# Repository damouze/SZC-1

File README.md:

# The Stackable Z80 Computer

A layman's attempt at designing a modular, stackable Z80 computer.

## Disclaimer

Let me start by pointing out that I am not an electronic engineer. Everything I know
about electronics I learned from the internet and from two electronic design courses
during my university days, and nearly all of it is theoretical. I am really more of a
software person who decided at one point in his not-so-distant past that it might be
fun to start learning to design (digital) electronic circuits. 

That said, this is not my first KiCAD project. 

The designs in this repository are bound to have many, many flaws, and I would love to
hear about them from you. Just keep in mind that I do have a day job and that it takes
precedence if I do not respond to them within a day. As a person without an actual
background in electronic design I am sure I am making assumptions about components in
the design that are incorrect or otherwise potentially troublesome. 

Ok, enough ranting. Let's have a look at it.

## Physical description

In principle, the Stackable Z80 computer is more an idea than an actual design. As such
it is built around the following concepts:

- The board dimensions are 95.25mm x 95.25mm (3.75" x 3.75")
- There are four main connectors:
    - Expansion Connector A (2x20 pins, IDC)
	- Expansion Connector B (2x17 pins, IDC)
	- Expansion Connector C (2x4 pins, IDC)
	- Power Connector (2x10 pins, IDC)
- Each board can be stacked on top of another through the use of standoffs

Expansion Connector A is standardized; it contains most, if not all, of the relevant
Z80 signals, such as the address bus (A0-A15), the data bus (D0-D7), control signals
like /INT, /RESET, etc, and both a CPU_CLK and a BUS_CLK signal (they may differ, but
the former should then always be an integer multiple of the latter). All address, data
and control lines should have pull-ups or pull-downs on at least one board, so as to
prevent undesirable current from flowing between two devices asserting the bus at the
same time. They are also buffered. Pins 1 and 40 are connected to ground.

Expansion Connector B is partly standardized; the uneven numbered pins are used for 8
interrupt lines (/INT0-/INT7), as well as 8 more address lines (MA14-A21). Pins 1 and 
34 are connected to ground. The remaining pins, all even, are defined as USER0-USER15,
or in other words, user defined. 

Expansion Connector C contains the extra bus signals provided by the Z80 CPU board with
an extended bus (cpu_board_ext_bus+v2). It provides 5 new signals: /IOR, /IOW, /MEMR, /MEMW
and /INTA. These can be used to simplify the designs of future boards. In addition they
also provide the necessary signals for interfacing with an Intel 8259 Programmable
Interrupt Controller. 

The Power Connector is standardized around the 20-pins ATX power supply connector, and indeed
the Power Board does contain one, but power to the CPU board is provided through an IDC header.
The rationale behind this is that power to the CPU board is is delivered from the power supply 
through the power board, which has a front panel header and which in turn distributes power to
the CPU board through the aforementioned 2x10 pins IDC header.

Power delivery to all other boards is standardized around the old-fashioned floppy 
connector (TE_171826-4). Only +12V and +5V are available. +5VSB (standby power) and 3.3V
should be delivered separately, for instance from the power board.

## Minimal configuration (top to bottom)

- Serial I/O board
- ROM/RAM board
- The "even simpler Z80" board
- Power board V2

This will provide a basic Z80 system with serial I/O support. The serial I/O board should
be configured to use /INT as its interrupt line and use 0x80 as its I/O base address.

The system will have 32kB of ROM, as well as 96kB of RAM, able to be paged in or out of the
Z80 address space as needed in segments of 16kB. 

Expansion Bus B is not used in this configuration.

## A more advance configuration (top to bottom)

- Serial I/O board
- ROM/RAM board v2
- CPU board with expansion Connector C
- Power board V2

This will provide a slightly more advanced Z80 system with serial I/O support. The serial I/O
board should be configured to use /INT as its interrupt line and use 0x80 as its I/O
base address. The ROM/RAM board should be configured for Bank 0. 

This system will have 512kB of Flash ROM and 1536kB of SRAM. Segments 0-31 will be ROM, 
segments 32-127 will be RAM. Segments 128-255 will be available for add-on boards with
their own ROM or RAM or which use memory mapped I/O. 

## Repository layout
 
The repository is laid out as follows:

- boards/core contains the core boards
    - even_simpler_z80: the basic, bare bones Z80 board; just the CPU, some buffers/latches and a clock generator
	- power_board: the power delivery board
	- power_board_v2: and updated version of the power delivery board, with power-on circuitry onboard
	- rom_ram_board: a board that provides 32kB of ROM and 96kB of RAM, able to be paged in and out as needed
	- serial_io_board: a board that provides a RS232 interface for outside communication
- boards/extra contains some extra board designs
    - 8259_pic_board: 8259 Interrupt Controller Board for the SZC-1; requires Expansion Connector C
    - audio_board: SSG Audio Board for the SZC-1, providing SSG sound support
	- cpu_board_ext_bus_v2: new and improved CPU board providing Expansion Connector C and an on-board memory mapper
    - diag_board: a basic diagnostics board, providing a 2-digit 7-segment display accessible through I/O port 0xb8
	- ide_board: IDE Board for the SZC-1, inspired by the Beer IDE interface for the MSX
	- mmu_board: a preliminary design for a Z80 MMU built around a ATF1502/1504 CPLD (*work in progress*)
	- rom_ram_board_2MB: a board that provides 512kB of flash ROM and 1536kB of RAM, able to be paged in and out as needed
	- rom_ram_board_128kB_v2: another board that provides 32kB of EEPROM and 96kB of RAM; requires Expansion Connector C
	- rom_ram_board_v2: another board that provides 512kB of flash ROM and 1536kB of RAM; requires Expansion Connector C
	- simple_z80: the original Z80 board, CPU, buffers/latches and a LS74xx based IM2 interrupt controller
- boards/msx_compat contains boards to provide MSX compatibility (*work in progress*)
    - msx_rom_board: a board that houses to 32kB EEPROM sockets for MSX compatible ROMs (requires the ppi_slot_select_expanded board)
    - msx_rom_ram_board: a board with 512kB flash ROM and 1MB SRAM (requires the ppi_slot_select_expanded board)
	- ppi_slot_select: a board that provides MSX compatible slot select registers as well as 16 GPIO pins
	- ppi_slot_select_expanded: as ppi_slot_select, but also contains an expanded slot select register
- digital contains experiments made in Digital to work out some concepts
- doc: contains documentation and other reference material
- ibom: interactive BOMs for the boards
- pics: 
    - renderings: contains 3D renderings of most of the boards
	- photos: contains photos of PCBs and assembled boards
- verilog: contains verilog output from Digital for the experiments in the *digital* folder.

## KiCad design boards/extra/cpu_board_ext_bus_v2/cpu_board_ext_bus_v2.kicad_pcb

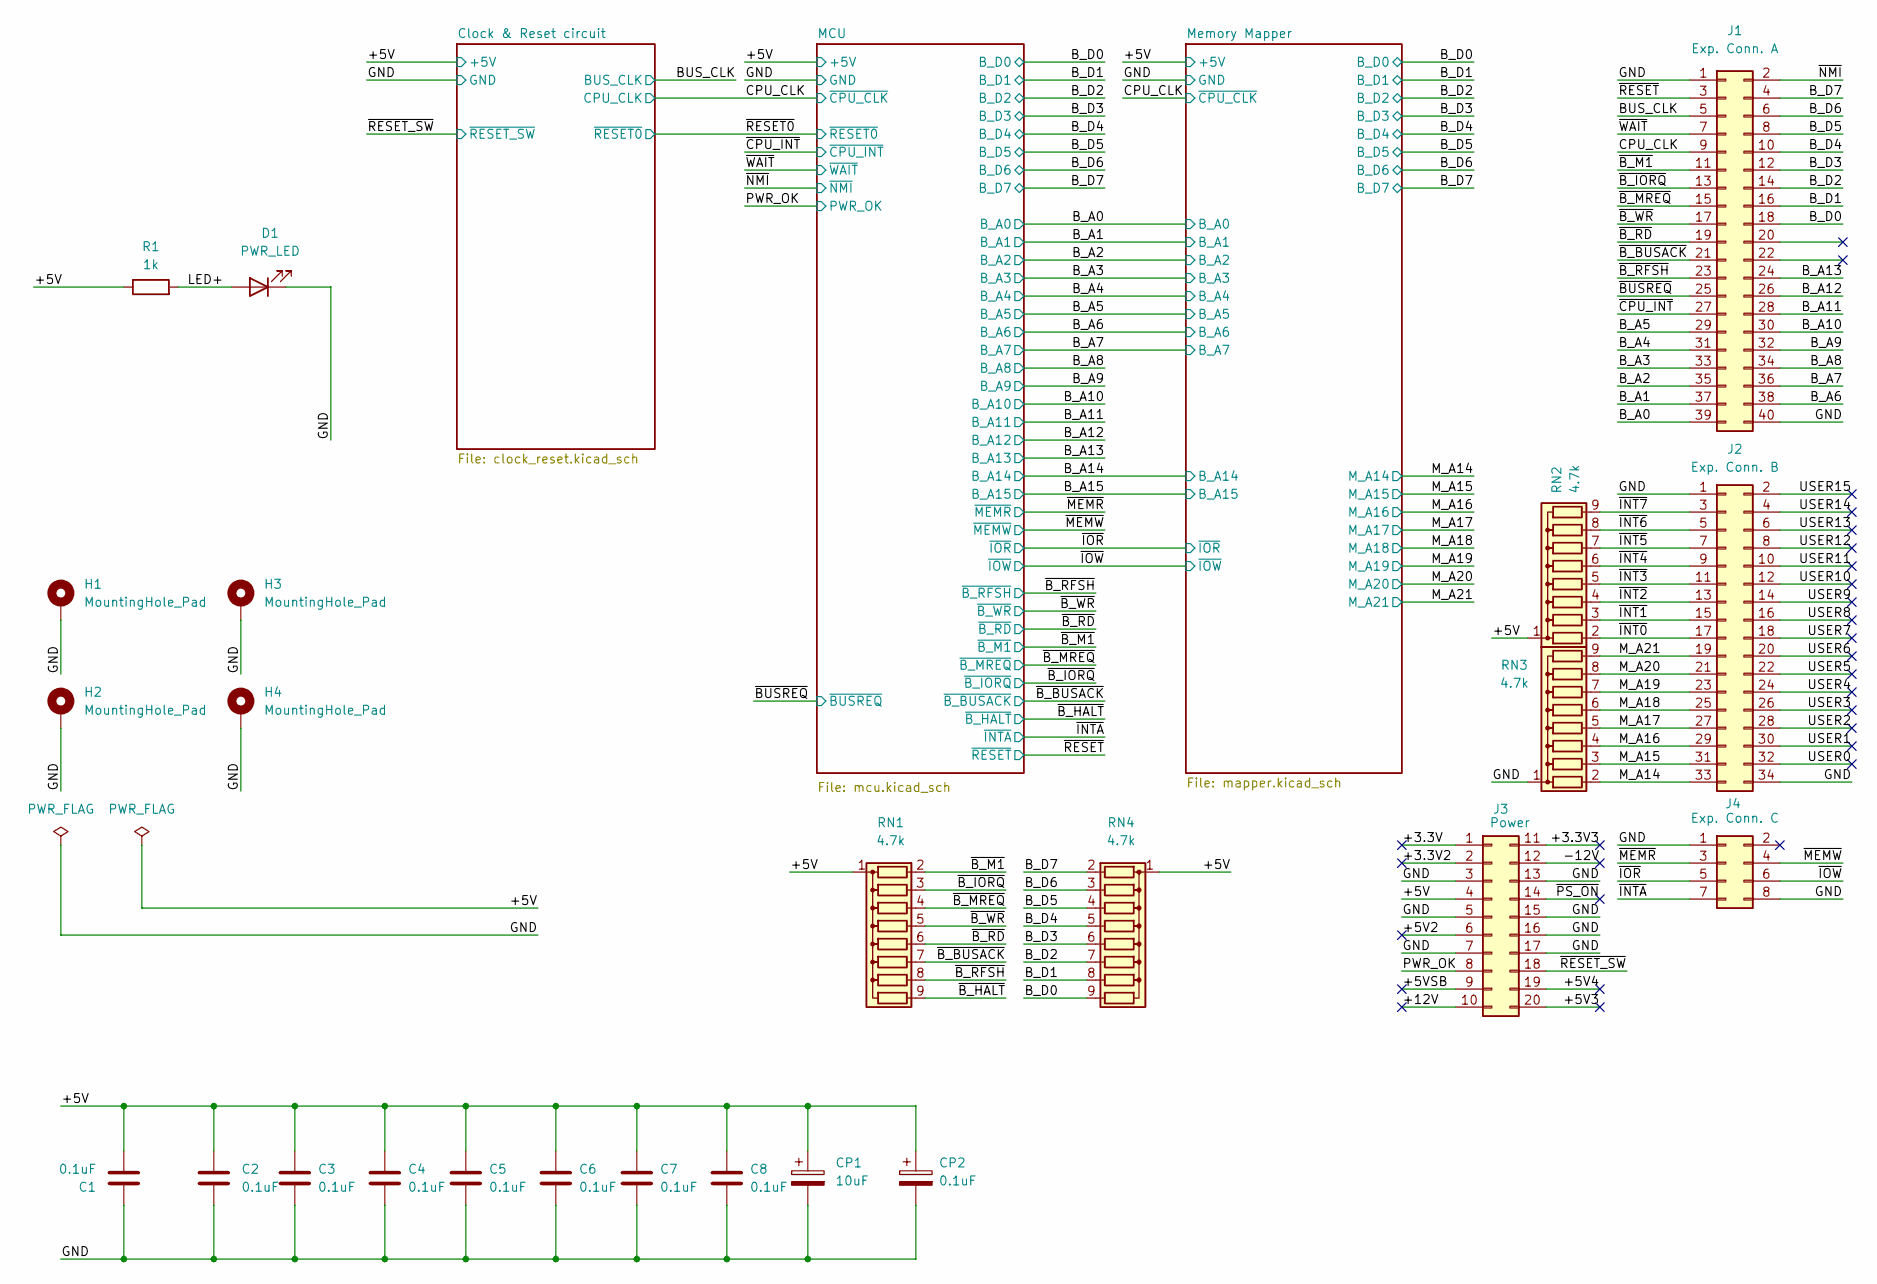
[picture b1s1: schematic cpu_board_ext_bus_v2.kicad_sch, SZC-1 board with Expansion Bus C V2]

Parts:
C1, C2, C3, C4, C5, C6, C7, C8: 0.1uF; C_Disc_D5.0mm_W2.5mm_P2.50mm; MPN FG28X7R1H104KNT06
CP1: 10uF; CP_Radial_D5.0mm_P2.50mm; MPN ECA1HM100I
CP2: 0.1uF; CP_Radial_D5.0mm_P2.50mm; MPN KS104M050C07RR0VH2FP0
D1: PWR_LED; LED_D3.0mm; MPN HLMP-1700
H1, H2, H3, H4: MountingHole_Pad; MountingHole_3.2mm_M3_ISO7380_Pad
J1: Exp. Conn. A; IDC-Header_2x20_P2.54mm_Horizontal; MPN X9555WR-2x20-6TV01
J2: Exp. Conn. B; IDC-Header_2x17_P2.54mm_Horizontal; MPN X9555WR-2x17-6TV01
J3: Power; IDC-Header_2x10_P2.54mm_Horizontal; MPN X9555WR-2x10-6TV01
J4: Exp. Conn. C; IDC-Header_2x04_P2.54mm_Horizontal; MPN 75867-132LF
R1: 1k; R_Axial_DIN0204_L3.6mm_D1.6mm_P7.62mm_Horizontal; MPN MBA02040C1001FC100
RN1, RN2, RN3, RN4: 4.7k; R_Array_SIP9; MPN A09-472JP

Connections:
/+3.3V: J3.1
/+3.3V2: J3.2
/+3.3V3: J3.11
/+5V: C1.1, C2.1, C3.1, C4.1, C5.1, C6.1, C7.1, C8.1, CP1.1, CP2.1, J3.4, R1.1, RN1.1 (common), RN2.1 (common), RN4.1 (common); also elsewhere on the board
/+5V2: J3.6
/+5V3: J3.20
/+5V4: J3.19
/+5VSB: J3.9
/+12V: J3.10
/-12V: J3.12
/BUS_CLK: J1.5; also elsewhere on the board
/B_A0: J1.39; also elsewhere on the board
/B_A1: J1.37; also elsewhere on the board
/B_A2: J1.35; also elsewhere on the board
/B_A3: J1.33; also elsewhere on the board
/B_A4: J1.31; also elsewhere on the board
/B_A5: J1.29; also elsewhere on the board
/B_A6: J1.38; also elsewhere on the board
/B_A7: J1.36; also elsewhere on the board
/B_A8: J1.34; also elsewhere on the board
/B_A9: J1.32; also elsewhere on the board
/B_A10: J1.30; also elsewhere on the board
/B_A11: J1.28; also elsewhere on the board
/B_A12: J1.26; also elsewhere on the board
/B_A13: J1.24; also elsewhere on the board
/B_D0: J1.18, RN4.9 (R8); also elsewhere on the board
/B_D1: J1.16, RN4.8 (R7); also elsewhere on the board
/B_D2: J1.14, RN4.7 (R6); also elsewhere on the board
/B_D3: J1.12, RN4.6 (R5); also elsewhere on the board
/B_D4: J1.10, RN4.5 (R4); also elsewhere on the board
/B_D5: J1.8, RN4.4 (R3); also elsewhere on the board
/B_D6: J1.6, RN4.3 (R2); also elsewhere on the board
/B_D7: J1.4, RN4.2 (R1); also elsewhere on the board
/CPU_CLK: J1.9; also elsewhere on the board
/GND: C1.2, C2.2, C3.2, C4.2, C5.2, C6.2, C7.2, C8.2, CP1.2, CP2.2, D1.1 (K), H1.1, H2.1, H3.1, H4.1, J1.1, J1.40, J2.1, J2.34, J3.3, J3.5, J3.7, J3.13, J3.15, J3.16, J3.17, J4.1, J4.8, RN3.1 (common); also elsewhere on the board
/LED+: D1.2 (A), R1.2
/M_A14: J2.33, RN3.2 (R1); also elsewhere on the board
/M_A15: J2.31, RN3.3 (R2); also elsewhere on the board
/M_A16: J2.29, RN3.4 (R3); also elsewhere on the board
/M_A17: J2.27, RN3.5 (R4); also elsewhere on the board
/M_A18: J2.25, RN3.6 (R5); also elsewhere on the board
/M_A19: J2.23, RN3.7 (R6); also elsewhere on the board
/M_A20: J2.21, RN3.8 (R7); also elsewhere on the board
/M_A21: J2.19, RN3.9 (R8); also elsewhere on the board
/PWR_OK: J3.8; also elsewhere on the board
/USER0: J2.32
/USER1: J2.30
/USER2: J2.28
/USER3: J2.26
/USER4: J2.24
/USER5: J2.22
/USER6: J2.20
/USER7: J2.18
/USER8: J2.16
/USER9: J2.14
/USER10: J2.12
/USER11: J2.10
/USER12: J2.8
/USER13: J2.6
/USER14: J2.4
/USER15: J2.2
/~BUSREQ: J1.25; also elsewhere on the board
/~B_BUSACK: J1.21, RN1.7 (R6); also elsewhere on the board
/~B_HALT: RN1.9 (R8); also elsewhere on the board
/~B_IORQ: J1.13, RN1.3 (R2); also elsewhere on the board
/~B_M1: J1.11, RN1.2 (R1); also elsewhere on the board
/~B_MREQ: J1.15, RN1.4 (R3); also elsewhere on the board
/~B_RD: J1.19, RN1.6 (R5); also elsewhere on the board
/~B_RFSH: J1.23, RN1.8 (R7); also elsewhere on the board
/~B_WR: J1.17, RN1.5 (R4); also elsewhere on the board
/~CPU_INT: J1.27; also elsewhere on the board
/~INT0: J2.17, RN2.2 (R1)
/~INT1: J2.15, RN2.3 (R2)
/~INT2: J2.13, RN2.4 (R3)
/~INT3: J2.11, RN2.5 (R4)
/~INT4: J2.9, RN2.6 (R5)
/~INT5: J2.7, RN2.7 (R6)
/~INT6: J2.5, RN2.8 (R7)
/~INT7: J2.3, RN2.9 (R8)
/~INTA: J4.7; also elsewhere on the board
/~IOR: J4.5; also elsewhere on the board
/~IOW: J4.6; also elsewhere on the board
/~MEMR: J4.3; also elsewhere on the board
/~MEMW: J4.4; also elsewhere on the board
/~NMI: J1.2; also elsewhere on the board
/~PS_ON: J3.14
/~RESET_SW: J3.18; also elsewhere on the board
/~RESET: J1.3; also elsewhere on the board
/~WAIT: J1.7; also elsewhere on the board

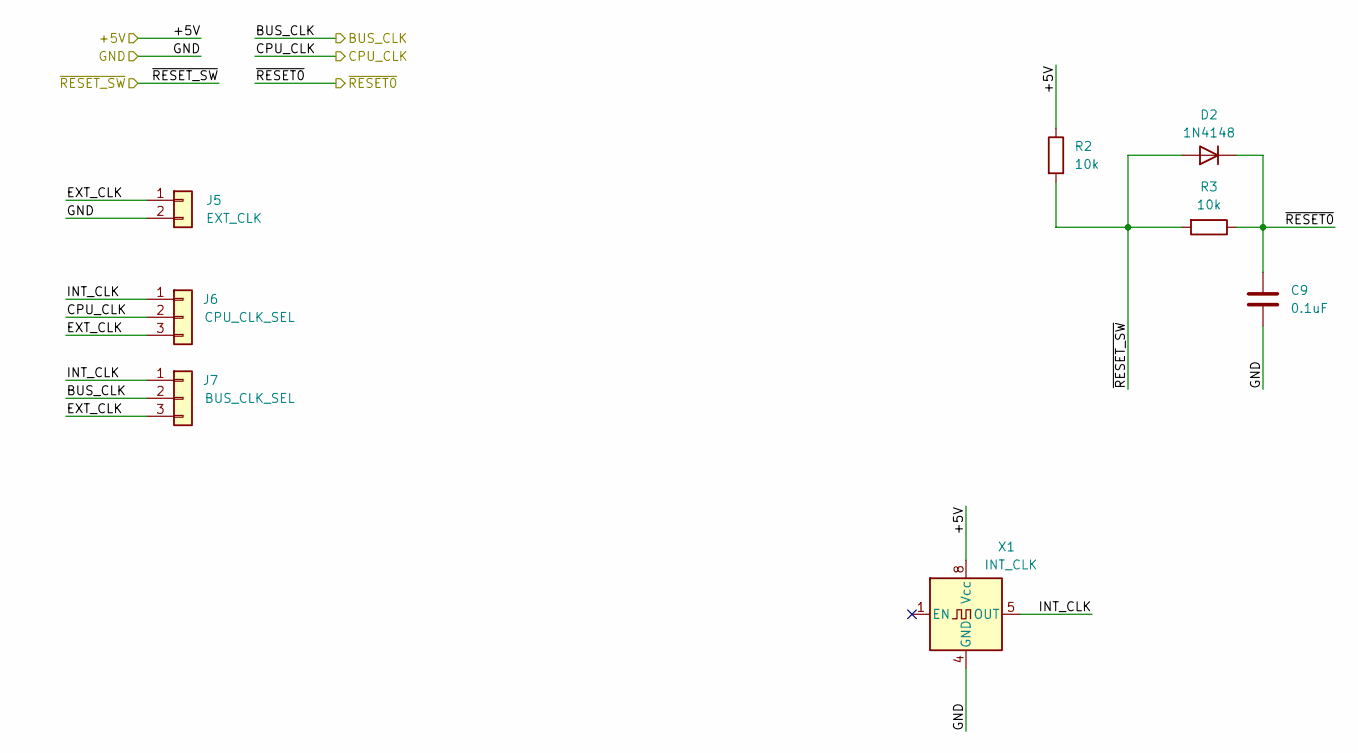
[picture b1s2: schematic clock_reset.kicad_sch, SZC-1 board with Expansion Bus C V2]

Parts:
C9: 0.1uF; C_Disc_D5.0mm_W2.5mm_P2.50mm; MPN FG28X7R1H104KNT06
D2: 1N4148; D_DO-35_SOD27_P7.62mm_Horizontal; MPN 1N4148TA
J5: EXT_CLK; PinHeader_1x02_P2.54mm_Horizontal; MPN PZ254R-11-02P
J6: CPU_CLK_SEL; PinHeader_1x03_P2.54mm_Horizontal; MPN PZ254R-11-03P
J7: BUS_CLK_SEL; PinHeader_1x03_P2.54mm_Horizontal; MPN PZ254R-11-03P
R2, R3: 10k; R_Axial_DIN0204_L3.6mm_D1.6mm_P7.62mm_Horizontal; MPN MBA02040C1002FRP00
X1: INT_CLK; Oscillator_DIP-8; MPN 1-2199298-2

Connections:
/+5V: R2.1, X1.8 (Vcc); also elsewhere on the board
/BUS_CLK: J7.2; also elsewhere on the board
/CPU_CLK: J6.2; also elsewhere on the board
/Clock & Reset circuit/EXT_CLK: J5.1, J6.3, J7.3
/Clock & Reset circuit/INT_CLK: J6.1, J7.1, X1.5 (OUT)
/GND: C9.2, J5.2, X1.4 (GND); also elsewhere on the board
/~RESET0: C9.1, D2.1 (K), R3.1; also elsewhere on the board
/~RESET_SW: D2.2 (A), R2.2, R3.2; also elsewhere on the board

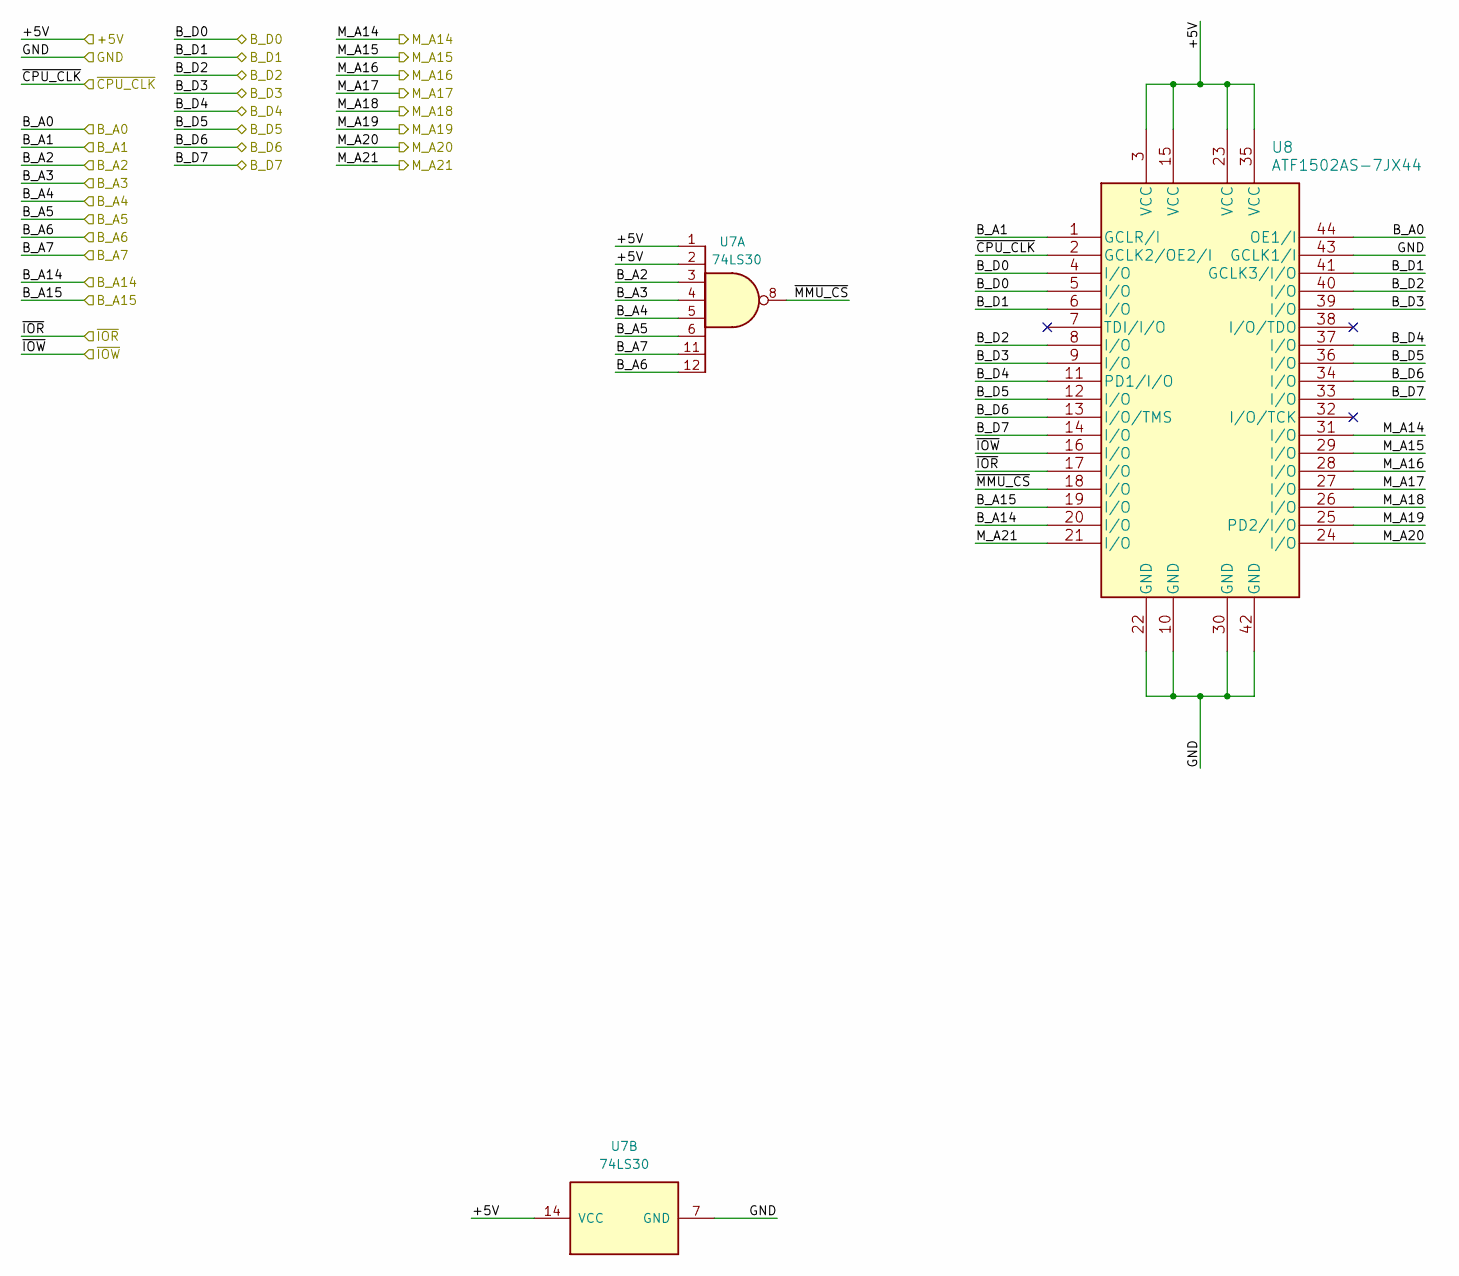
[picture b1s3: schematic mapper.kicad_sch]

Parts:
U7: 74LS30; DIP-14_W7.62mm_Socket; MPN 1-2199298-3
U8: ATF1502AS-7JX44; PLCC-44_THT-Socket; MPN DS1032-44SDKT1A

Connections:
/+5V: U7.1, U7.2, U7.14 (VCC), U8.3 (VCC), U8.15 (VCC), U8.23 (VCC), U8.35 (VCC); also elsewhere on the board
/B_A0: U8.44 (OE1/I); also elsewhere on the board
/B_A1: U8.1 (GCLR/I); also elsewhere on the board
/B_A2: U7.3; also elsewhere on the board
/B_A3: U7.4; also elsewhere on the board
/B_A4: U7.5; also elsewhere on the board
/B_A5: U7.6; also elsewhere on the board
/B_A6: U7.12; also elsewhere on the board
/B_A7: U7.11; also elsewhere on the board
/B_A14: U8.20 (I/O); also elsewhere on the board
/B_A15: U8.19 (I/O); also elsewhere on the board
/B_D0: U8.4 (I/O), U8.5 (I/O); also elsewhere on the board
/B_D1: U8.6 (I/O), U8.41 (GCLK3/I/O); also elsewhere on the board
/B_D2: U8.8 (I/O), U8.40 (I/O); also elsewhere on the board
/B_D3: U8.9 (I/O), U8.39 (I/O); also elsewhere on the board
/B_D4: U8.11 (PD1/I/O), U8.37 (I/O); also elsewhere on the board
/B_D5: U8.12 (I/O), U8.36 (I/O); also elsewhere on the board
/B_D6: U8.13 (I/O/TMS), U8.34 (I/O); also elsewhere on the board
/B_D7: U8.14 (I/O), U8.33 (I/O); also elsewhere on the board
/CPU_CLK: U8.2 (GCLK2/OE2/I); also elsewhere on the board
/GND: U7.7 (GND), U8.10 (GND), U8.22 (GND), U8.30 (GND), U8.42 (GND), U8.43 (GCLK1/I); also elsewhere on the board
/M_A14: U8.31 (I/O); also elsewhere on the board
/M_A15: U8.29 (I/O); also elsewhere on the board
/M_A16: U8.28 (I/O); also elsewhere on the board
/M_A17: U8.27 (I/O); also elsewhere on the board
/M_A18: U8.26 (I/O); also elsewhere on the board
/M_A19: U8.25 (PD2/I/O); also elsewhere on the board
/M_A20: U8.24 (I/O); also elsewhere on the board
/M_A21: U8.21 (I/O); also elsewhere on the board
/Memory Mapper/~MMU_CS: U7.8, U8.18 (I/O)
/~IOR: U8.17 (I/O); also elsewhere on the board
/~IOW: U8.16 (I/O); also elsewhere on the board

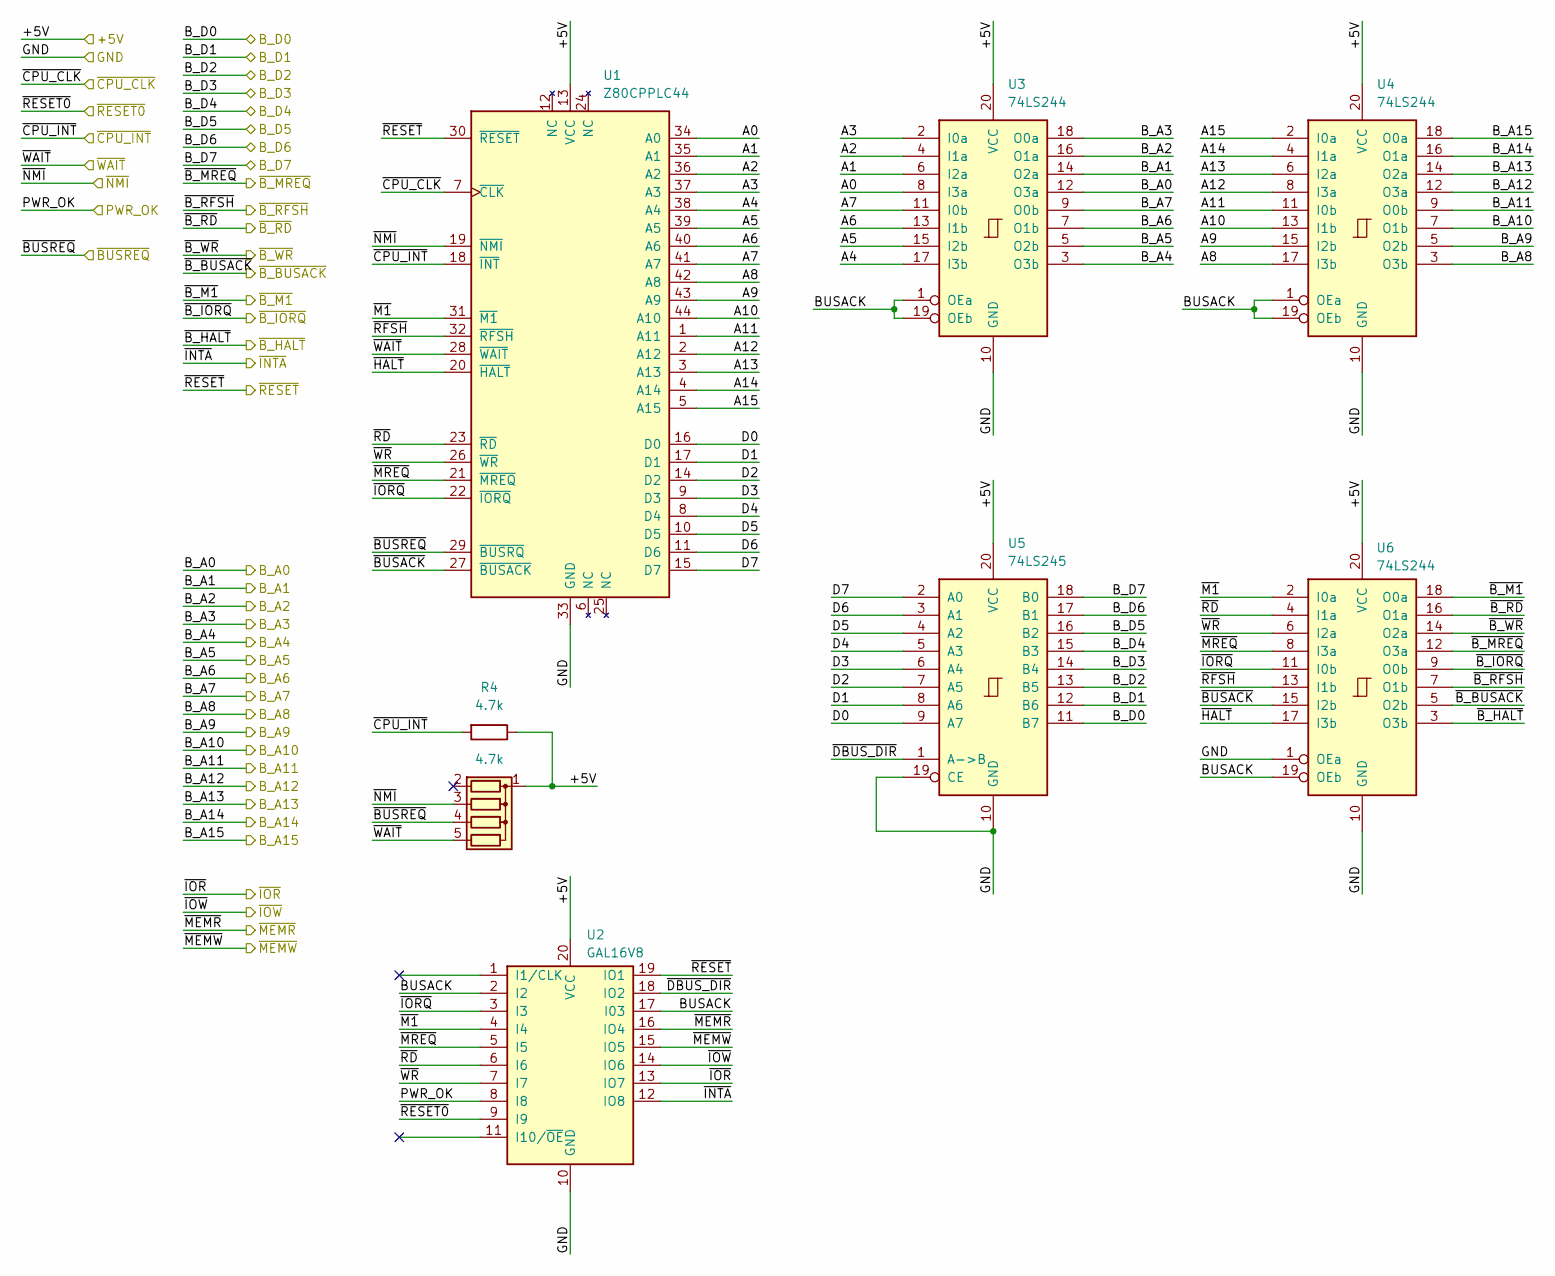
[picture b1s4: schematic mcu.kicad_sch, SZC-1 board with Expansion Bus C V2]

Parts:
R4: 4.7k; R_Axial_DIN0204_L3.6mm_D1.6mm_P7.62mm_Horizontal; MPN MF0207FTE52-4K7
RN5: 4.7k; R_Array_SIP5; MPN A05-472JP
U1: Z80CPPLC44; PLCC-44_THT-Socket; MPN DS1032-44SDKT1A
U2: GAL16V8; DIP-20_W7.62mm_Socket; MPN 1-2199298-6
U3, U4, U6: 74LS244; DIP-20_W7.62mm_Socket; MPN 1-2199298-6
U5: 74LS245; DIP-20_W7.62mm_Socket; MPN 1-2199298-6

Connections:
/+5V: R4.1, RN5.1 (common), U1.13 (VCC), U2.20 (VCC), U3.20 (VCC), U4.20 (VCC), U5.20 (VCC), U6.20 (VCC); also elsewhere on the board
/B_A0: U3.12 (O3a); also elsewhere on the board
/B_A1: U3.14 (O2a); also elsewhere on the board
/B_A2: U3.16 (O1a); also elsewhere on the board
/B_A3: U3.18 (O0a); also elsewhere on the board
/B_A4: U3.3 (O3b); also elsewhere on the board
/B_A5: U3.5 (O2b); also elsewhere on the board
/B_A6: U3.7 (O1b); also elsewhere on the board
/B_A7: U3.9 (O0b); also elsewhere on the board
/B_A8: U4.3 (O3b); also elsewhere on the board
/B_A9: U4.5 (O2b); also elsewhere on the board
/B_A10: U4.7 (O1b); also elsewhere on the board
/B_A11: U4.9 (O0b); also elsewhere on the board
/B_A12: U4.12 (O3a); also elsewhere on the board
/B_A13: U4.14 (O2a); also elsewhere on the board
/B_A14: U4.16 (O1a); also elsewhere on the board
/B_A15: U4.18 (O0a); also elsewhere on the board
/B_D0: U5.11 (B7); also elsewhere on the board
/B_D1: U5.12 (B6); also elsewhere on the board
/B_D2: U5.13 (B5); also elsewhere on the board
/B_D3: U5.14 (B4); also elsewhere on the board
/B_D4: U5.15 (B3); also elsewhere on the board
/B_D5: U5.16 (B2); also elsewhere on the board
/B_D6: U5.17 (B1); also elsewhere on the board
/B_D7: U5.18 (B0); also elsewhere on the board
/CPU_CLK: U1.7 (~CLK); also elsewhere on the board
/GND: U1.33 (GND), U2.10 (GND), U3.10 (GND), U4.10 (GND), U5.10 (GND), U5.19 (CE), U6.1 (OEa), U6.10 (GND); also elsewhere on the board
/MCU/A0: U1.34 (A0), U3.8 (I3a)
/MCU/A1: U1.35 (A1), U3.6 (I2a)
/MCU/A2: U1.36 (A2), U3.4 (I1a)
/MCU/A3: U1.37 (A3), U3.2 (I0a)
/MCU/A4: U1.38 (A4), U3.17 (I3b)
/MCU/A5: U1.39 (A5), U3.15 (I2b)
/MCU/A6: U1.40 (A6), U3.13 (I1b)
/MCU/A7: U1.41 (A7), U3.11 (I0b)
/MCU/A8: U1.42 (A8), U4.17 (I3b)
/MCU/A9: U1.43 (A9), U4.15 (I2b)
/MCU/A10: U1.44 (A10), U4.13 (I1b)
/MCU/A11: U1.1 (A11), U4.11 (I0b)
/MCU/A12: U1.2 (A12), U4.8 (I3a)
/MCU/A13: U1.3 (A13), U4.6 (I2a)
/MCU/A14: U1.4 (A14), U4.4 (I1a)
/MCU/A15: U1.5 (A15), U4.2 (I0a)
/MCU/BUSACK: U2.2 (I2), U2.17 (I03), U3.1 (OEa), U3.19 (OEb), U4.1 (OEa), U4.19 (OEb), U6.19 (OEb)
/MCU/D0: U1.16 (D0), U5.9 (A7)
/MCU/D1: U1.17 (D1), U5.8 (A6)
/MCU/D2: U1.14 (D2), U5.7 (A5)
/MCU/D3: U1.9 (D3), U5.6 (A4)
/MCU/D4: U1.8 (D4), U5.5 (A3)
/MCU/D5: U1.10 (D5), U5.4 (A2)
/MCU/D6: U1.11 (D6), U5.3 (A1)
/MCU/D7: U1.15 (D7), U5.2 (A0)
/MCU/~BUSACK: U1.27 (~BUSACK), U6.15 (I2b)
/MCU/~DBUS_DIR: U2.18 (IO2), U5.1 (A->B)
/MCU/~HALT: U1.20 (~HALT), U6.17 (I3b)
/MCU/~IORQ: U1.22 (~IORQ), U2.3 (I3), U6.11 (I0b)
/MCU/~M1: U1.31 (~M1), U2.4 (I4), U6.2 (I0a)
/MCU/~MREQ: U1.21 (~MREQ), U2.5 (I5), U6.8 (I3a)
/MCU/~RD: U1.23 (~RD), U2.6 (I6), U6.4 (I1a)
/MCU/~RFSH: U1.32 (~RFSH), U6.13 (I1b)
/MCU/~WR: U1.26 (~WR), U2.7 (I7), U6.6 (I2a)
/PWR_OK: U2.8 (I8); also elsewhere on the board
/~BUSREQ: RN5.4 (R3), U1.29 (~BUSRQ); also elsewhere on the board
/~B_BUSACK: U6.5 (O2b); also elsewhere on the board
/~B_HALT: U6.3 (O3b); also elsewhere on the board
/~B_IORQ: U6.9 (O0b); also elsewhere on the board
/~B_M1: U6.18 (O0a); also elsewhere on the board
/~B_MREQ: U6.12 (O3a); also elsewhere on the board
/~B_RD: U6.16 (O1a); also elsewhere on the board
/~B_RFSH: U6.7 (O1b); also elsewhere on the board
/~B_WR: U6.14 (O2a); also elsewhere on the board
/~CPU_INT: R4.2, U1.18 (~INT); also elsewhere on the board
/~INTA: U2.12 (IO8); also elsewhere on the board
/~IOR: U2.13 (IO7); also elsewhere on the board
/~IOW: U2.14 (IO6); also elsewhere on the board
/~MEMR: U2.16 (IO4); also elsewhere on the board
/~MEMW: U2.15 (IO5); also elsewhere on the board
/~NMI: RN5.3 (R2), U1.19 (~NMI); also elsewhere on the board
/~RESET0: U2.9 (I9); also elsewhere on the board
/~RESET: U1.30 (~RESET), U2.19 (IO1); also elsewhere on the board
/~WAIT: RN5.5 (R4), U1.28 (~WAIT); also elsewhere on the board

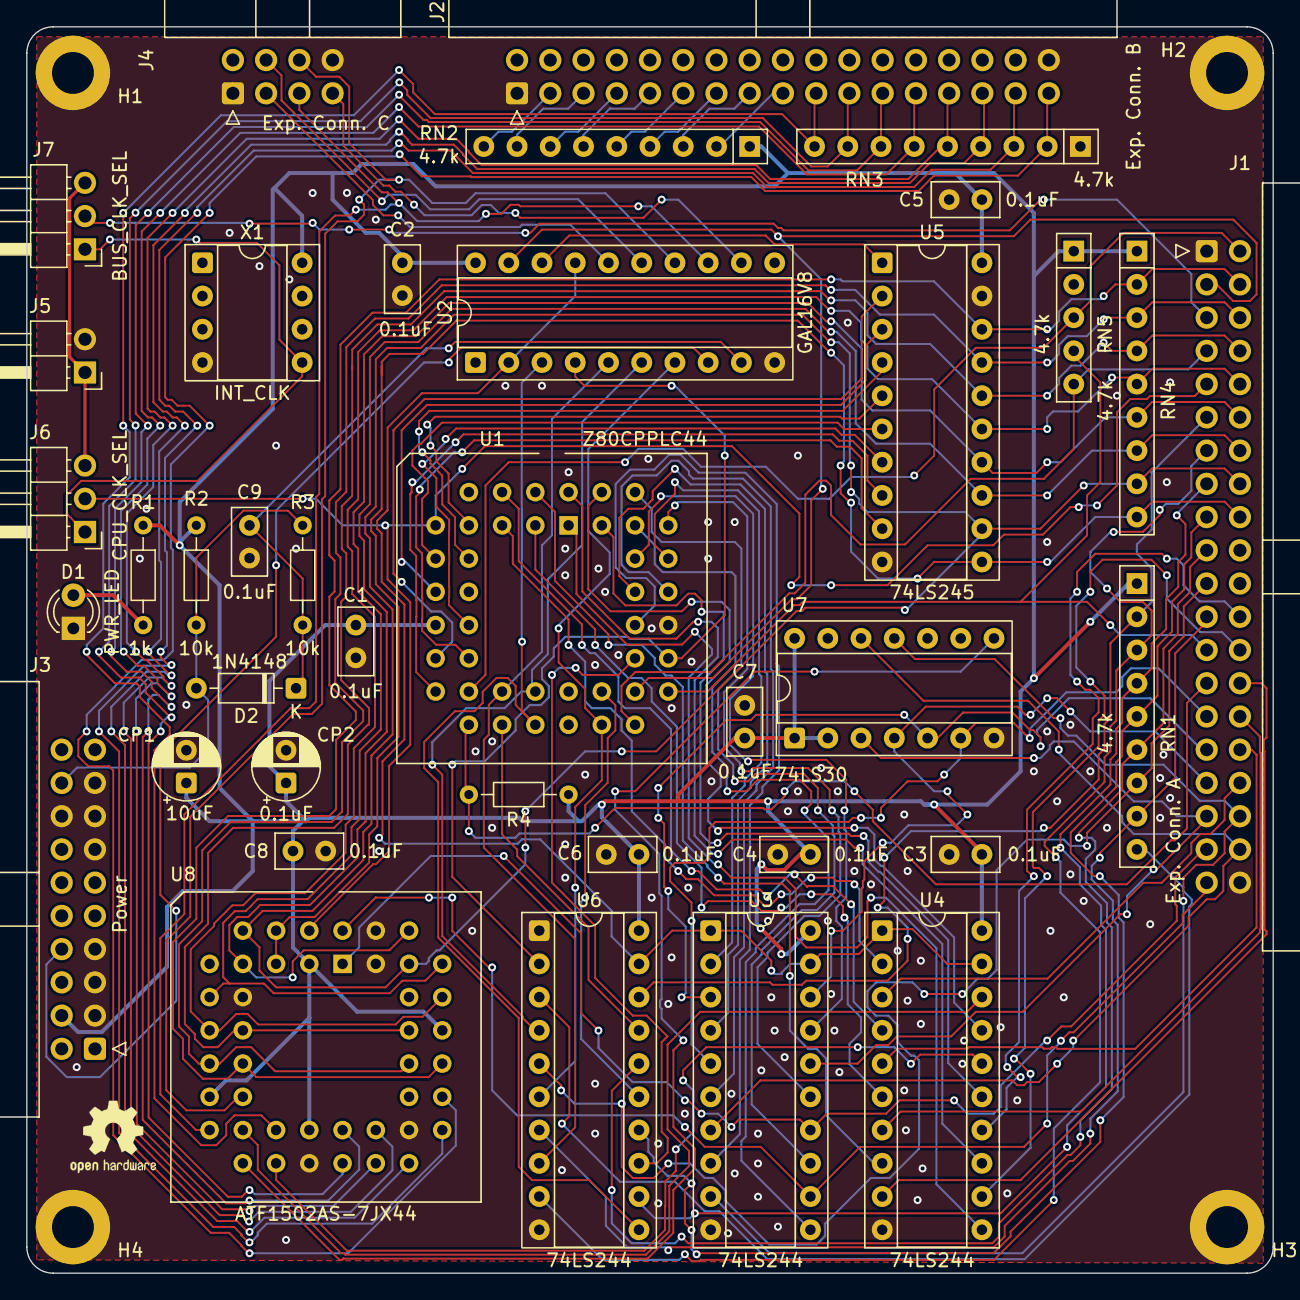
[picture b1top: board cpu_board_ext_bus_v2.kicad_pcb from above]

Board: 2 copper layers, 95.2 x 95.2 mm, 42 parts (0 on the bottom side), 103 nets.

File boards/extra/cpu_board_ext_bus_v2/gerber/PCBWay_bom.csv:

designator,quantity,value,pack,mpn,mount_type
"C1, C2, C3, C4, C5, C6, C7, C8, C9",9,0.1uF,C_Disc_D5.0mm_W2.5mm_P2.50mm,FG28X7R1H104KNT06,tht
CP1,1,10uF,CP_Radial_D5.0mm_P2.50mm,ECA1HM100I,tht
CP2,1,0.1uF,CP_Radial_D5.0mm_P2.50mm,KS104M050C07RR0VH2FP0,tht
D1,1,PWR_LED,LED_D3.0mm,HLMP-1700,tht
D2,1,1N4148,D_DO-35_SOD27_P7.62mm_Horizontal,1N4148TA,tht
"H1, H2, H3, H4",4,MountingHole_Pad,MountingHole_3.2mm_M3_ISO7380_Pad,,tht
J1,1,Exp. Conn. A,IDC-Header_2x20_P2.54mm_Horizontal,X9555WR-2x20-6TV01,tht
J2,1,Exp. Conn. B,IDC-Header_2x17_P2.54mm_Horizontal,X9555WR-2x17-6TV01,tht
J3,1,Power,IDC-Header_2x10_P2.54mm_Horizontal,X9555WR-2x10-6TV01,tht
J4,1,Exp. Conn. C,IDC-Header_2x04_P2.54mm_Horizontal,75867-132LF,tht
J5,1,EXT_CLK,PinHeader_1x02_P2.54mm_Horizontal,PZ254R-11-02P,tht
J6,1,CPU_CLK_SEL,PinHeader_1x03_P2.54mm_Horizontal,PZ254R-11-03P ,tht
J7,1,BUS_CLK_SEL,PinHeader_1x03_P2.54mm_Horizontal,PZ254R-11-03P,tht
R1,1,1k,R_Axial_DIN0204_L3.6mm_D1.6mm_P7.62mm_Horizontal,MFR2WSFTE73-1K,tht
"R2, R3",2,10k,R_Axial_DIN0204_L3.6mm_D1.6mm_P7.62mm_Horizontal,MFR3WSFTE73-10K,tht
R4,1,4.7k,R_Axial_DIN0204_L3.6mm_D1.6mm_P7.62mm_Horizontal,MF0207FTE52-4K7,tht
"RN1, RN2, RN3, RN4",4,4.7k,R_Array_SIP9,A09-472JP,tht
RN5,1,4.7k,R_Array_SIP5,A05-472JP,tht
U1,1,Z80CPPLC44,PLCC-44_THT-Socket,DS1032-44SDKT1A,tht
U2,1,GAL16V8,DIP-20_W7.62mm_Socket,1-2199298-6,tht
"U3, U4, U6",3,74LS244,DIP-20_W7.62mm_Socket,1-2199298-6,tht
U5,1,74LS245,DIP-20_W7.62mm_Socket,1-2199298-6,tht
U7,1,74LS30,DIP-14_W7.62mm_Socket,1-2199298-3,tht
U8,1,ATF1502AS-7JX44,PLCC-44_THT-Socket,DS1032-44SDKT1A,tht
X1,1,INT_CLK,DIP-8_W7.62mm_Socket,1-2199298-2,tht

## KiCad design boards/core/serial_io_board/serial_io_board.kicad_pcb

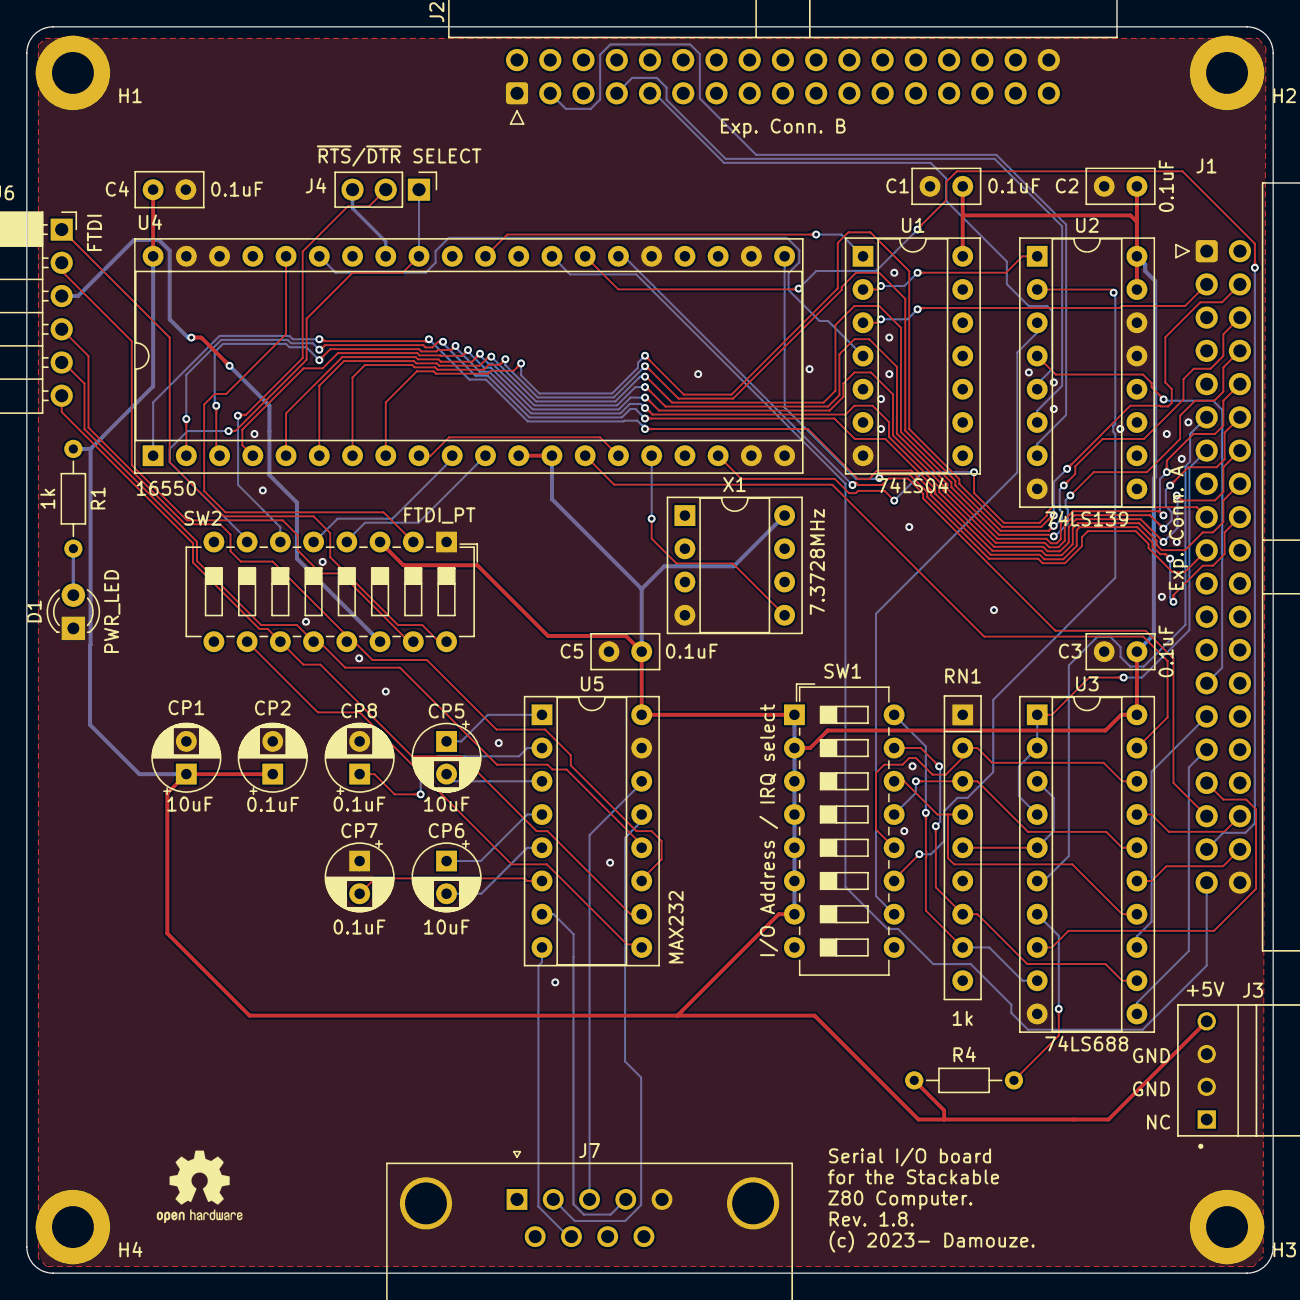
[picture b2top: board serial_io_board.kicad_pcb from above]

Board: 2 copper layers, 95.2 x 95.2 mm, 33 parts (0 on the bottom side), 66 nets.

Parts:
C1, C2, C3, C4, C5: 0.1uF; C_Disc_D5.0mm_W2.5mm_P2.50mm
CP1, CP5, CP6: 10uF; CP_Radial_D5.0mm_P2.50mm
CP2, CP7, CP8: 0.1uF; CP_Radial_D5.0mm_P2.50mm
D1: PWR_LED; LED_D3.0mm
H1, H2, H3, H4: MountingHole_Pad; MountingHole_3.2mm_M3_ISO7380_Pad
J1: Exp. Conn. A; IDC-Header_2x20_P2.54mm_Horizontal
J2: Exp. Conn. B; IDC-Header_2x17_P2.54mm_Horizontal
J3: Power; TE_171826-4
J4: ~{RTS}/~{DTR} SELECT; PinHeader_1x03_P2.54mm_Vertical
J6: FTDI; PinSocket_1x06_P2.54mm_Horizontal
J7: COM1; DSUB-9_Male_Horizontal_P2.77x2.84mm_EdgePinOffset4.94mm_Hou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
R1: 1k; R_Axial_DIN0204_L3.6mm_D1.6mm_P7.62mm_Horizontal
R4: 4.7k; R_Axial_DIN0204_L3.6mm_D1.6mm_P7.62mm_Horizontal
RN1: 1k; R_Array_SIP9
SW1: I/O Address / IRQ select; SW_DIP_SPSTx08_Slide_6.7x21.88mm_W7.62mm_P2.54mm_LowProfile
SW2: FTDI_PT; SW_DIP_SPSTx08_Slide_6.7x21.88mm_W7.62mm_P2.54mm_LowProfile
U1: 74LS04; DIP-14_W7.62mm_Socket
U2: 74LS139; DIP-16_W7.62mm_Socket
U3: 74LS688; DIP-20_W7.62mm_Socket
U4: 16550; DIP-40_W15.24mm_Socket
U5: MAX232; DIP-16_W7.62mm_Socket
X1: 7.3728MHz; DIP-8_W7.62mm_Socket

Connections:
/+5V: C1.1, C2.1, C3.1, C4.1, C5.1, CP1.1, CP2.1, J3.4, R1.1, R4.1, SW1.1, SW1.2, SW1.3, SW1.4, SW1.5, SW1.6, SW1.7, SW2.3, U1.14 (VCC), U2.15 (E), U2.16 (VCC), U3.20 (VCC), U4.12 (CS0), U4.13 (CS1), U4.40 (VCC), U5.16 (VCC), X1.8 (Vcc)
/B_A0: J1.39, U4.28 (A0)
/B_A1: J1.37, U4.27 (A1)
/B_A2: J1.35, U4.26 (A2)
/B_A3: J1.33, U3.8 (P3)
/B_A4: J1.31, U3.11 (P4)
/B_A5: J1.29, U3.13 (P5)
/B_A6: J1.38, U3.15 (P6)
/B_A7: J1.36, U3.17 (P7)
/B_D0: J1.18, U4.1 (D0)
/B_D1: J1.16, U4.2 (D1)
/B_D2: J1.14, U4.3 (D2)
/B_D3: J1.12, U4.4 (D3)
/B_D4: J1.10, U4.5 (D4)
/B_D5: J1.8, U4.6 (D5)
/B_D6: J1.6, U4.7 (D6)
/B_D7: J1.4, U4.8 (D7)
/FTDI_VCC: J6.3, SW2.14
/GND: C1.2, C2.2, C3.2, C4.2, C5.2, CP1.2, CP2.2, CP7.1, CP8.2, D1.1 (K), H1.1, H2.1, H3.1, H4.1, J1.1, J1.40, J2.1, J2.34, J3.2, J3.3, J7.0 (PAD), J7.5, RN1.1 (common), SW2.1, U1.7 (GND), U2.8 (GND), U2.13 (A1), U2.14 (A0), U3.10 (GND), U4.19 (WR), U4.20 (GND), U4.22 (RD), U4.25 (~ADS), U4.38 (~DCD), U4.39 (~RI), U5.15 (GND), X1.4 (GND)
/IRQ0_S: SW1.11, U2.2 (A0)
/IRQ1_S: SW1.10, U2.3 (A1)
/RX: J6.5, SW2.12, U5.12 (R1OUT)
/R_A3: RN1.8 (R7), SW1.16, U3.9 (R3)
/R_A4: RN1.7 (R6), SW1.15, U3.12 (R4)
/R_A5: RN1.4 (R3), SW1.14, U3.14 (R5)
/R_A6: RN1.3 (R2), SW1.13, U3.16 (R6)
/R_A7: RN1.2 (R1), SW1.12, U3.18 (R7)
/S_DTR: J7.4, U5.7 (T2OUT)
/S_RTS: J7.7, U5.8 (R2IN)
/S_RX: J7.2, U5.13 (R1IN)
/S_TX: J7.3, U5.14 (T1OUT)
/TX: J6.4, SW2.13, U5.11 (T1IN)
/UART_CLK: U4.16 (XIN), X1.5 (OUT)
/UART_INT: U1.1, U4.30 (INTR)
/UART_RESET: U1.4, U4.35 (MR)
/UART_SIN: SW2.5, U4.10 (SIN)
/UART_SOUT: SW2.4, U4.11 (SOUT)
/~BAUDOUT: U4.9 (RCLK), U4.15 (~BAUDOUT)
/~B_IORQ: J1.13, U3.1 (G), U3.2 (P0), U3.4 (P1)
/~B_M1: J1.11, U3.6 (P2)
/~B_RD: J1.19, U4.21 (~RD)
/~B_WR: J1.17, U4.18 (~WR)
/~CTS: J6.2, SW2.15
/~DTR: J6.6, SW2.11, U5.10 (T2IN)
/~FTDI_DTR: J4.2, SW2.6
/~INT4: J2.9, U2.5 (O1)
/~INT5: J2.7, U2.6 (O2)
/~INT7: J2.3, U2.7 (O3)
/~INT: J1.27, U2.4 (O0)
/~RESET: J1.3, U1.3
/~RTS: SW2.10, U5.9 (R2OUT)
/~R_IORQ: RN1.5 (R4), U3.3 (R0), U3.5 (R1)
/~R_M1: R4.2, U3.7 (R2)
/~UART_CS: U3.19 (P=R), U4.14 (~CS2)
/~UART_CTS: SW2.2, U4.36 (~CTS)
/~UART_DTR: J4.3, U4.33 (~DTR)
/~UART_INT: U1.2, U2.1 (E)
/~UART_RTS: J4.1, SW2.7, U4.32 (~RTS)
unnamed: D1.2 (A), R1.2
unnamed: J6.1, SW2.16
unnamed: CP5.1, U5.1 (C1+)
unnamed: CP5.2, U5.3 (C1-)
unnamed: CP6.1, U5.4 (C2+)
unnamed: CP6.2, U5.5 (C2-)
unnamed: CP8.1, U5.2 (VS+)
unnamed: CP7.2, U5.6 (VS-)

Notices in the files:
boards/core/serial_io_board/serial_io_board.kicad_pcb:
(c) 2023- Damouze.
boards/extra/cpu_board_ext_bus_v2/cpu_board_ext_bus_v2.kicad_pcb:
(c) 2024-  Damouze
